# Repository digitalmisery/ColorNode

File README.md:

ColorNode
=========

Replacement wireless controller for GE ColorEffects Lights

Additional info on the [ColorNode](http://www.digitalmisery.com/projects/colornode/) project page.

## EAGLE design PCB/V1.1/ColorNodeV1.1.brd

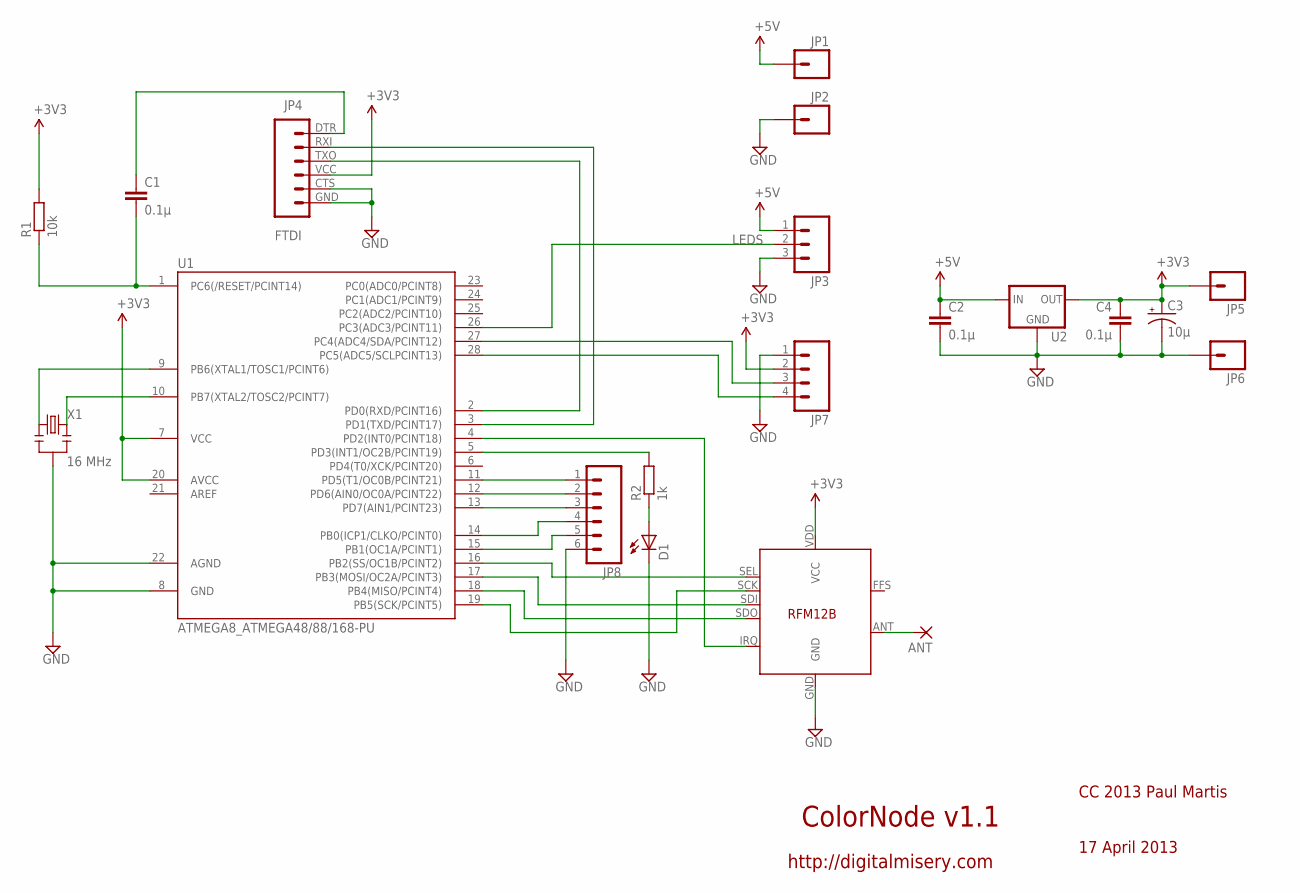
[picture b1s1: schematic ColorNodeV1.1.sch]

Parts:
ANT: 1,6/0,8
C1, C2, C4: 0.1µ; C025-024X044
C3: 10µ; E1,8-4
D1: LED3MM
JP1, JP2: M01PTH_2MM; 1X01_2MM
JP3: M031X03_NO_SILK; 1X03_NO_SILK
JP4: FTDI; FTDI_BASIC
JP5, JP6: M01PTH; 1X01
JP7: M041X04_NO_SILK; 1X04_NO_SILK
JP8: M06SIP; 1X06
R1: 10k; 0204/7
R2: 1k; 0204/7
U1: ATMEGA8_ATMEGA48/88/168-PU; ATMEGA8_DIL28-3
U2: MCP1700INLINE; TO92-INLINE
U3: RFM12B
X1: 16 MHz; RESONATOR-PTH

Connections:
5V: C2.1, JP1.1, JP3.1, U2.2 (IN)
GND: C2.2, C3.-, C4.2, D1.K (C), JP2.1, JP3.3, JP4.CTS (5), JP4.GND (6), JP6.1, JP7.1, JP8.6, U1.8 (GND), U1.22 (AGND), U2.1 (GND), U3.GND, X1.2
LEDS: JP3.2, U1.26 (PC3(ADC3/PCINT11))
unnamed: U1.9 (PB6(XTAL1/TOSC1/PCINT6)), X1.1
unnamed: JP8.2, U1.12 (PD6(AIN0/OC0A/PCINT22))
unnamed: C1.1, JP4.DTR (1)
unnamed: JP8.5, U1.15 (PB1(OC1A/PCINT1))
unnamed: C1.2, R1.1, U1.1 (PC6(/RESET/PCINT14))
unnamed: JP4.TXO (3), U1.2 (PD0(RXD/PCINT16))
unnamed: JP4.RXI (2), U1.3 (PD1(TXD/PCINT17))
unnamed: U1.17 (PB3(MOSI/OC2A/PCINT3)), U3.SDI
unnamed: U1.4 (PD2(INT0/PCINT18)), U3.IRQ
unnamed: U1.18 (PB4(MISO/PCINT4)), U3.SDO
unnamed: U1.19 (PB5(SCK/PCINT5)), U3.SCK
unnamed: ANT.1, U3.ANT
unnamed: U1.16 (PB2(SS/OC1B/PCINT2)), U3.SEL
unnamed: JP7.3, U1.27 (PC4(ADC4/SDA/PCINT12))
unnamed: JP7.4, U1.28 (PC5(ADC5/SCLPCINT13))
unnamed: JP8.4, U1.14 (PB0(ICP1/CLKO/PCINT0))
unnamed: JP8.3, U1.13 (PD7(AIN1/PCINT23))
unnamed: JP8.1, U1.11 (PD5(T1/OC0B/PCINT21))
unnamed: D1.A, R2.1
unnamed: U1.10 (PB7(XTAL2/TOSC2/PCINT7)), X1.3
unnamed: R2.2, U1.5 (PD3(INT1/OC2B/PCINT19))
VCC: C3.+, C4.1, JP4.VCC (4), JP5.1, JP7.2, R1.2, U1.7 (VCC), U1.20 (AVCC), U2.3 (OUT), U3.VDD (VCC)

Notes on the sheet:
ColorNode v1.1
CC 2013 Paul Martis
http://digitalmisery.com
17 April 2013

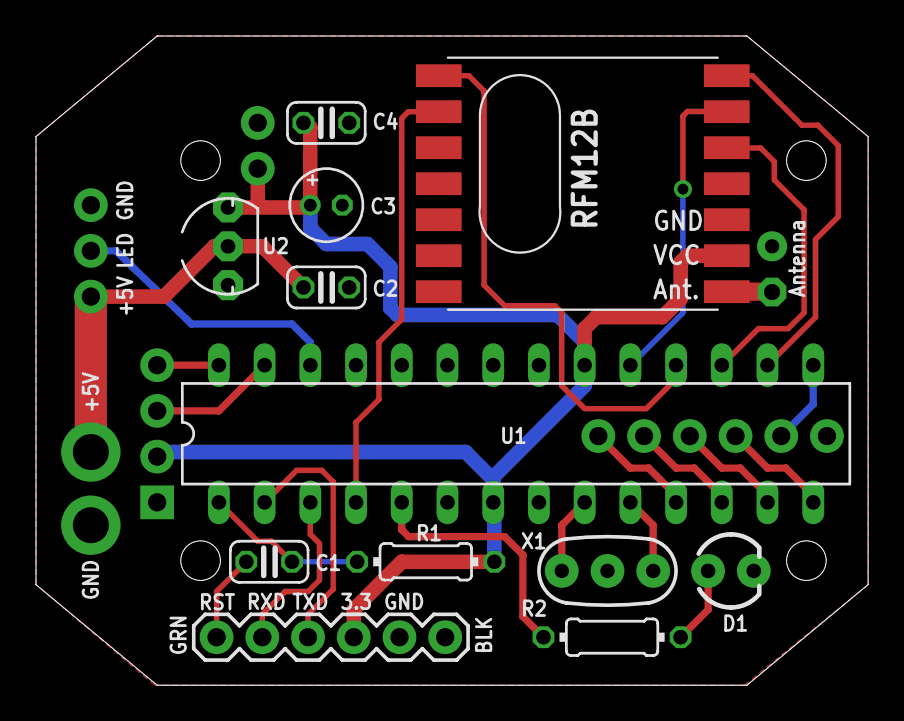
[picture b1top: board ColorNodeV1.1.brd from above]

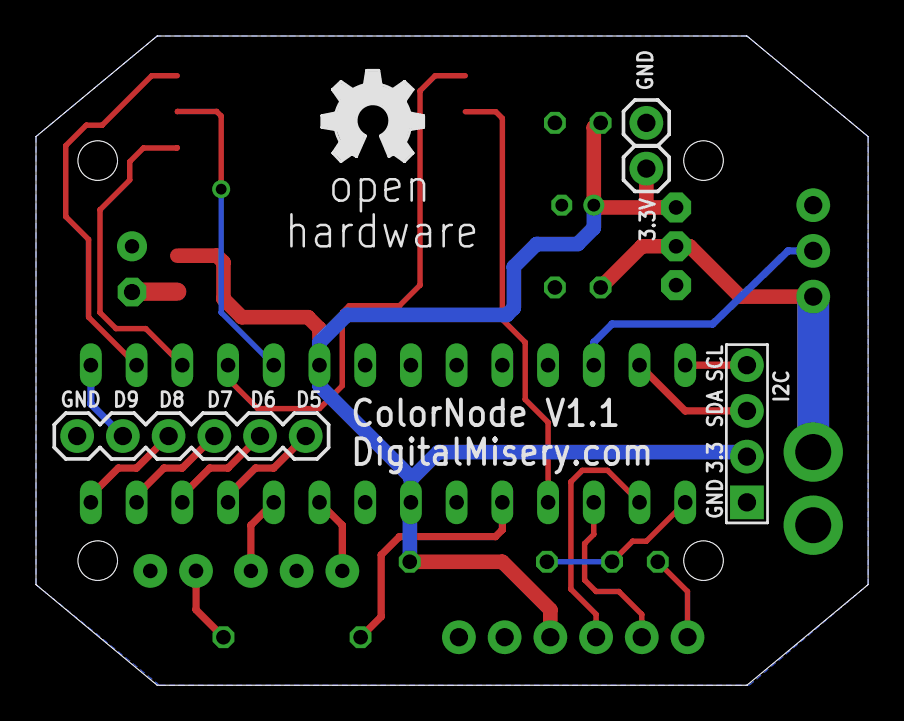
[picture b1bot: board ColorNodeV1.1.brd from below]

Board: 2 copper layers, 46.2 x 36.1 mm, 21 parts (4 on the bottom side), 25 nets.

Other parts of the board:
E$2: OSHW_FILLX200_NOTEXT

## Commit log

2013-08-02 Added code examples and V1.1 Eagle PCB design files.

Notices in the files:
parts and their libraries:
SparkFun-LED: Licensing: CC v3.0 Share-Alike You are welcome to use this library for commercial purposes.
